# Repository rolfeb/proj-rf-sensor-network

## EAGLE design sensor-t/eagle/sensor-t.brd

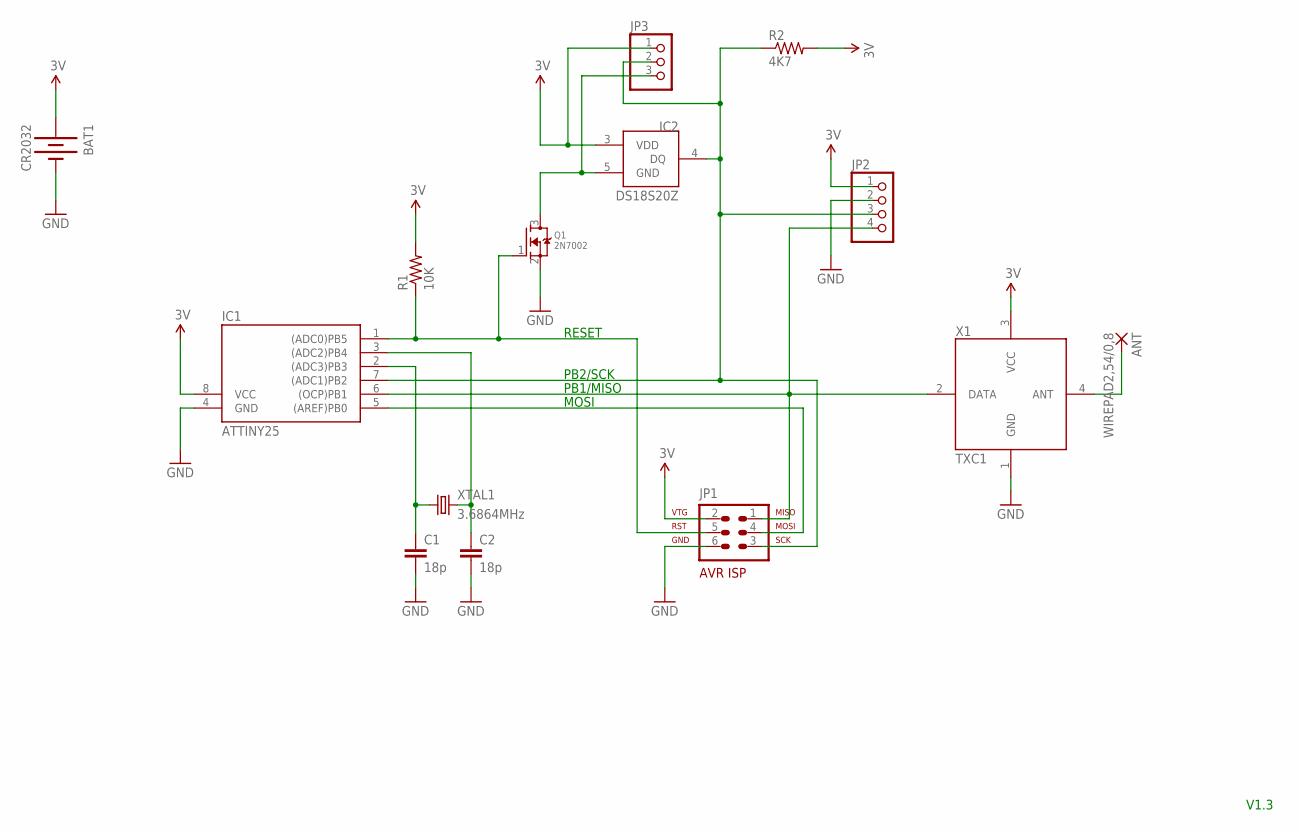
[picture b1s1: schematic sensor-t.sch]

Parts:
ANT: WIREPAD2,54/0,8; 2,54/0,8
BAT1: CR2032; BATTCON_CELL_20MM
C1, C2: 18p; 0805
IC1: ATTINY25; SOIC8
IC2: DS18S20Z; SO08-208
JP1: AVR-ISP-6X1; 1X06
JP2: PINHD-1X4; 1X04
JP3: PINHD-1X3; 1X03
Q1: 2N7002; SOT23
R1: 10K; M0805
R2: 4K7; M0805
X1: TXC1
XTAL1: 3.6864MHz; HC49UP

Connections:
3.3V: BAT1.+VE (+), IC1.8 (VCC), IC2.3 (VDD), JP1.2, JP2.1, JP3.1, R1.2, R2.2, X1.3 (VCC)
GND: BAT1.-VE (-), C1.2, C2.2, IC1.4 (GND), JP1.6, JP2.2, Q1.2 (S), X1.1 (GND)
unnamed: IC1.6 ((OCP)PB1), JP1.1, JP2.4, X1.2 (DATA)
unnamed: IC1.5 ((AREF)PB0), JP1.4
unnamed: ANT.1, X1.4 (ANT)
unnamed: IC1.1 ((ADC0)PB5), JP1.5, Q1.1 (G), R1.1
unnamed: C1.1, IC1.2 ((ADC3)PB3), XTAL1.1
unnamed: C2.1, IC1.3 ((ADC2)PB4), XTAL1.2
unnamed: IC1.7 ((ADC1)PB2), IC2.4 (DQ), JP1.3, JP2.3, JP3.2, R2.1
unnamed: IC2.5 (GND), JP3.3, Q1.3 (D)

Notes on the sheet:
V1.3
RESET
PB2/SCK
PB1/MISO
MOSI

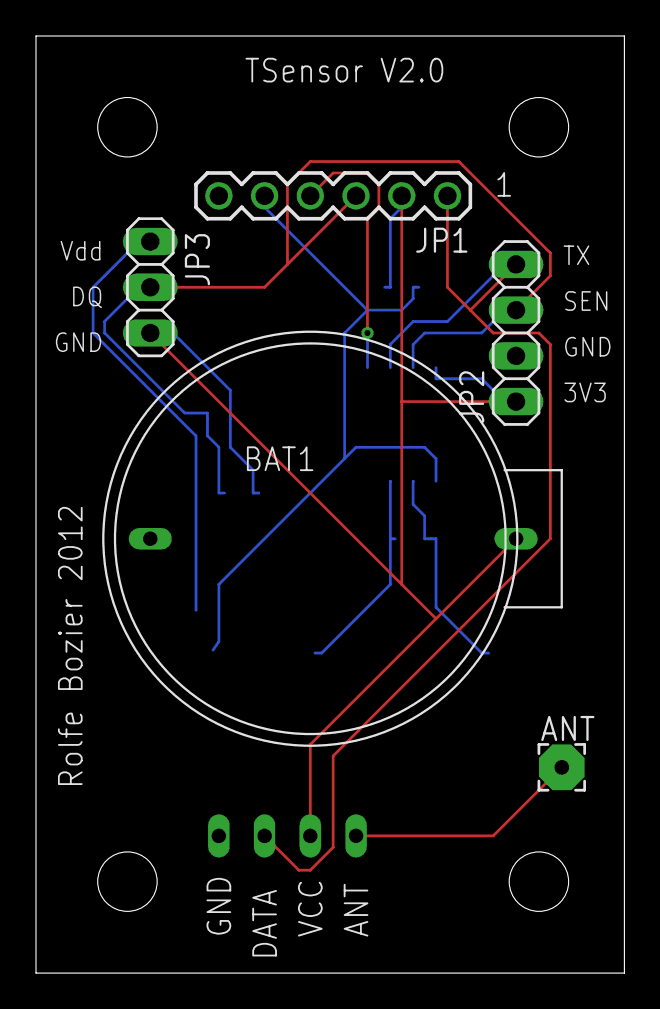
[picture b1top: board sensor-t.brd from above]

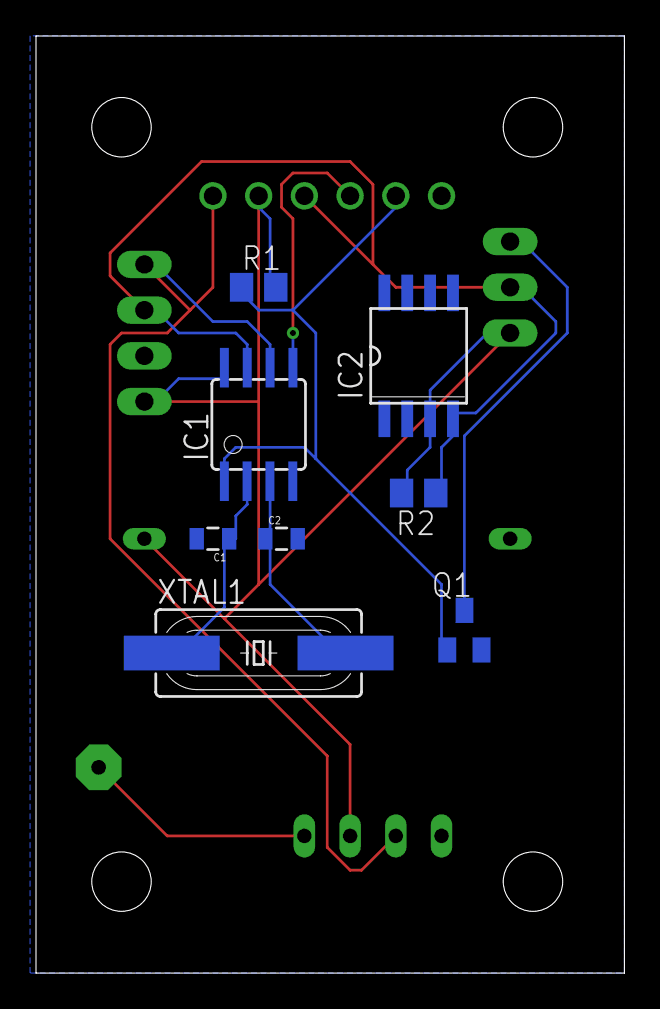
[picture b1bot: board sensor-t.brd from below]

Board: 2 copper layers, 32.7 x 52.1 mm, 18 parts (8 on the bottom side), 10 nets.

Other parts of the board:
U$1, U$2, U$3, U$4: STAND-OFF

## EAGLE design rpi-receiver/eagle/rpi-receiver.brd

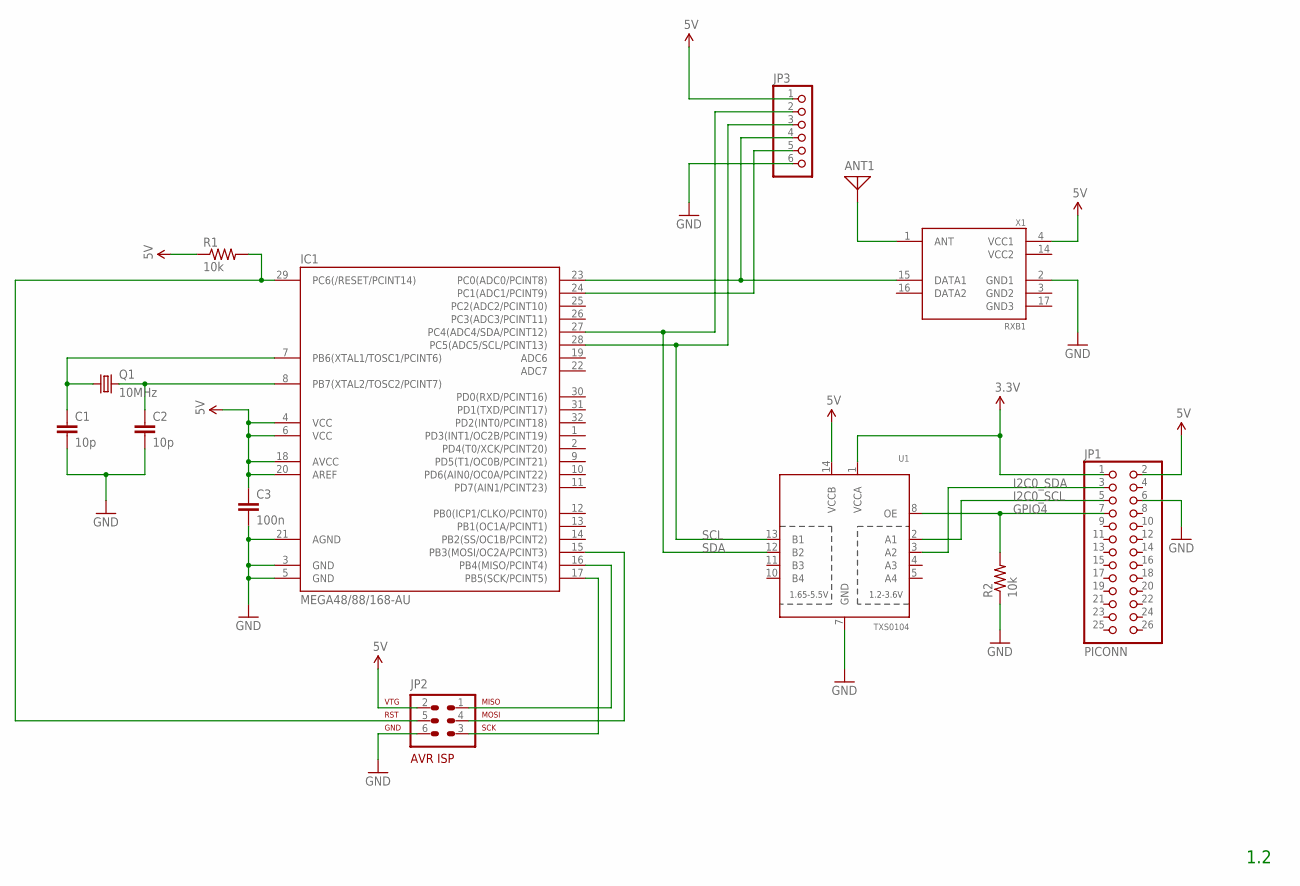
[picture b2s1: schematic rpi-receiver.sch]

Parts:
ANT1: ANTENNA; PAD-01
C1, C2: 10p; C0805
C3: 100n; C0805
IC1: MEGA48/88/168-AU; TQFP32-08
JP1: PICONN; 2X13
JP2: AVR-ISP-6POL-HDR; 22-23-2061
JP3: PINHD-1X6; 1X06
Q1: 10MHz; HC49UP
R1, R2: 10k; M0805
U1: TXS0104; TSSOP14
X1: RXB1

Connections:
3.3V: JP1.1, U1.1 (VCCA)
5V: C3.1, IC1.4 (VCC), IC1.6 (VCC), IC1.18 (AVCC), IC1.20 (AREF), JP1.2, JP2.2, JP3.1, R1.1, U1.14 (VCCB), X1.4 (VCC1)
GND: C1.2, C2.2, C3.2, IC1.3 (GND), IC1.5 (GND), IC1.21 (AGND), JP1.6, JP2.6, JP3.6, R2.1, U1.7 (GND), X1.2 (GND1)
GND2: X1.3 (GND2)
GND3: X1.17 (GND3)
GPIO4: JP1.7, R2.2, U1.8 (OE)
I2C0_SCL: JP1.5, U1.2 (A1)
I2C0_SDA: JP1.3, U1.3 (A2)
unnamed: C2.1, IC1.8 (PB7(XTAL2/TOSC2/PCINT7)), Q1.2
unnamed: C1.1, IC1.7 (PB6(XTAL1/TOSC1/PCINT6)), Q1.1
unnamed: IC1.16 (PB4(MISO/PCINT4)), JP2.1
unnamed: IC1.15 (PB3(MOSI/OC2A/PCINT3)), JP2.4
unnamed: ANT1.1, X1.1 (ANT)
unnamed: IC1.29 (PC6(/RESET/PCINT14)), JP2.5, R1.2
unnamed: IC1.17 (PB5(SCK/PCINT5)), JP2.3
unnamed: IC1.24 (PC1(ADC1/PCINT9)), JP3.5
unnamed: IC1.23 (PC0(ADC0/PCINT8)), JP3.4, X1.15 (DATA1)
SCL: IC1.28 (PC5(ADC5/SCL/PCINT13)), JP3.3, U1.13 (B1)
SDA: IC1.27 (PC4(ADC4/SDA/PCINT12)), JP3.2, U1.12 (B2)
VCC2: X1.14 (VCC2)

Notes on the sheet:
1.2

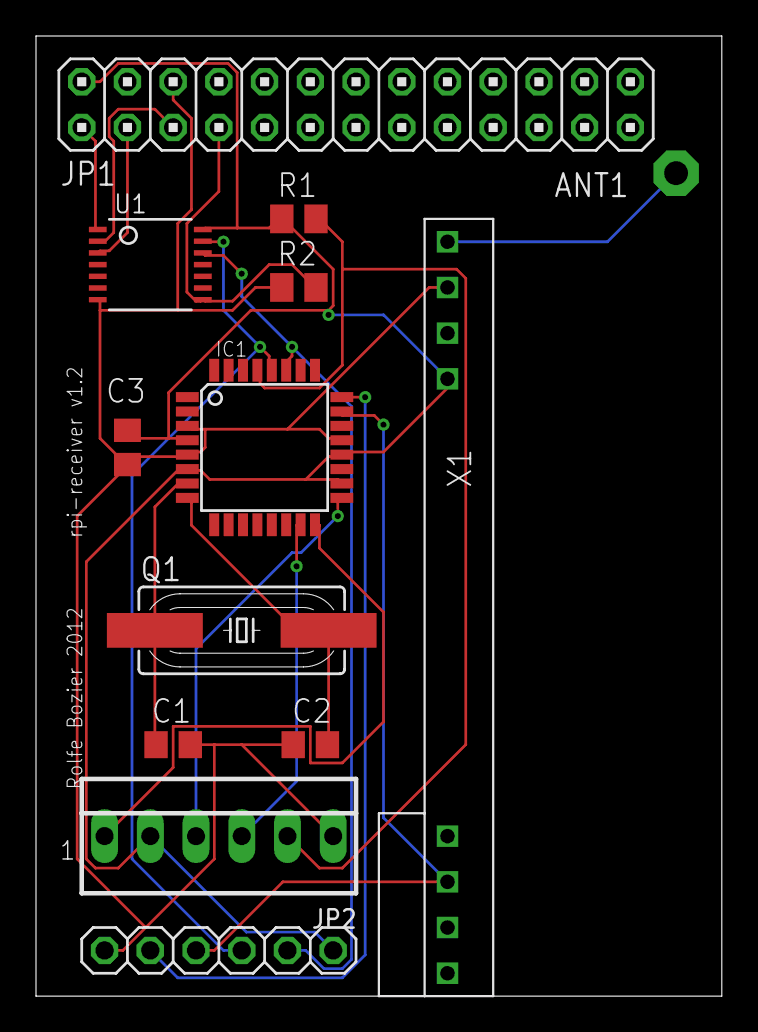
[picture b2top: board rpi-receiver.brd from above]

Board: 2 copper layers, 38.1 x 53.3 mm, 13 parts (0 on the bottom side), 17 nets.

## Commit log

2014-12-20 Initial commit.
2014-12-21 Some cleanup and documentation.
2015-02-09 Renamed LICENSE to UNLICENSE
2015-02-09 Added link to more information
2016-03-10 Added new sensor for battery voltage. Measure the battery voltage every hour and include in message.
2016-03-13 Added sensor daemon and database creation scripts.
2016-03-13 Added a brief note about the sensord daemon.
2016-03-13 Moved rpi-tools/db up 1 level.
2016-03-24 Added logwatch, logrotate configuration information.
2023-09-10 Committed outstanding changes
